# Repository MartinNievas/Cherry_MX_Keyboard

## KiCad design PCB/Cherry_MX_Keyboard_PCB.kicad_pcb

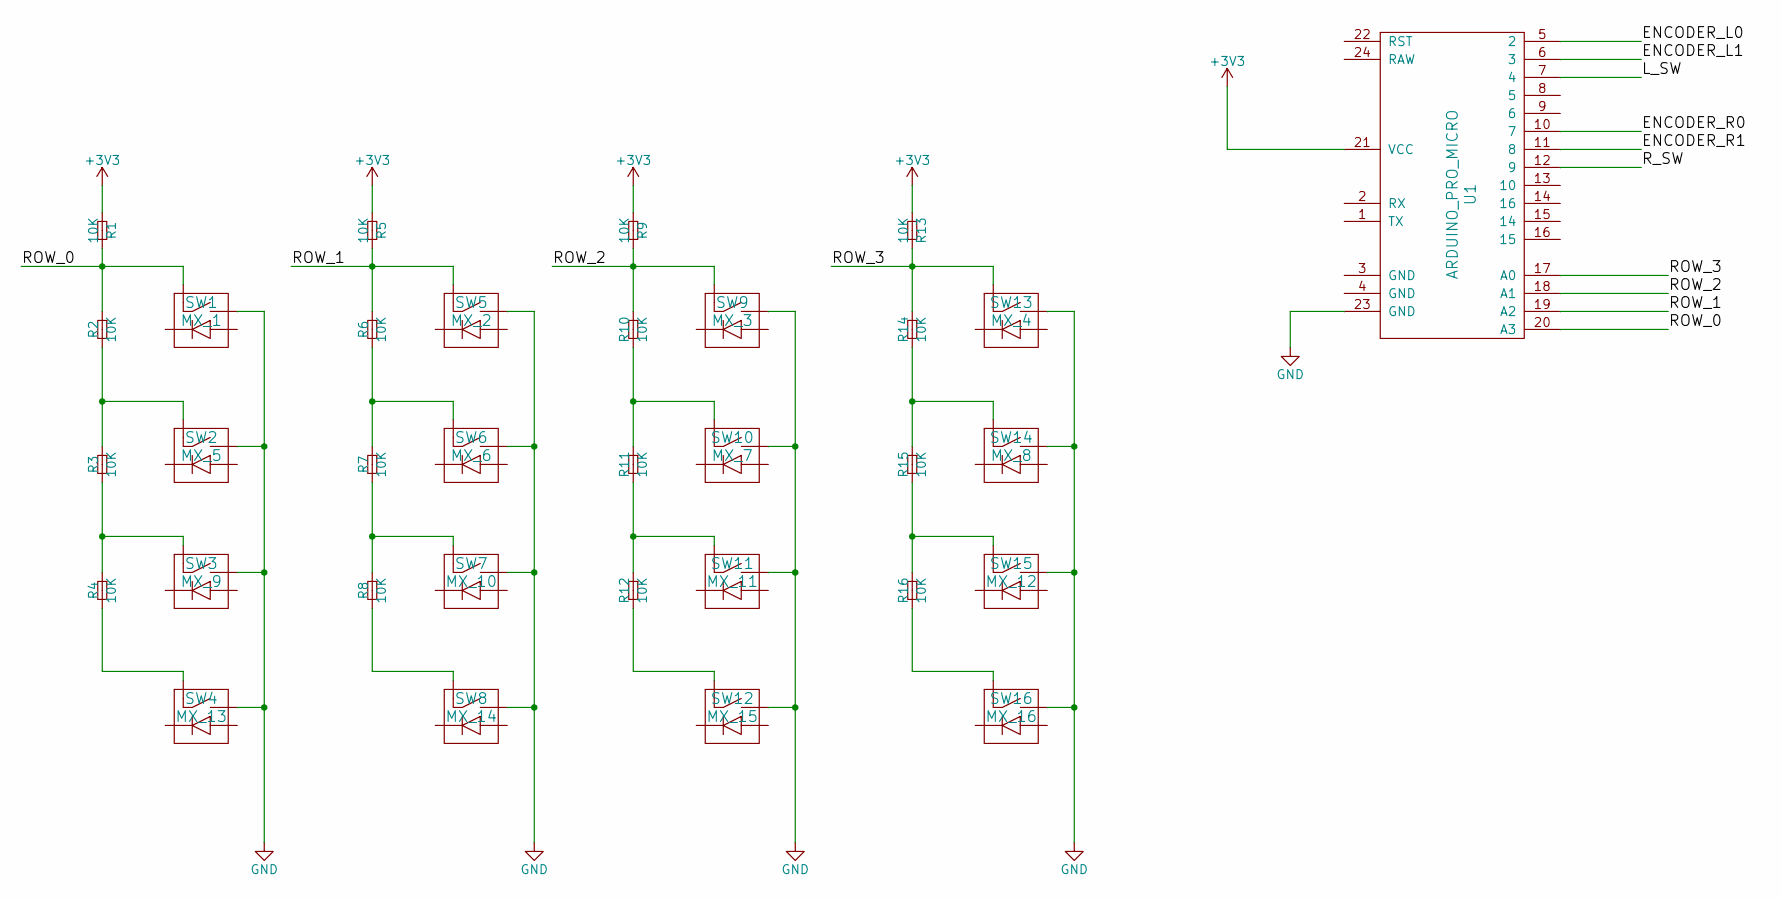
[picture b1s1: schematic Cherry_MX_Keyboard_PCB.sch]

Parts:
R1, R2, R3, R4, R5, R6, R7, R8, R9, R10, R11, R12, R13, R14, R15, R16: 10K; R4
SW1: MX_1; SW_PCB_4PIN
SW2: MX_5; SW_PCB_4PIN
SW3: MX_9; SW_PCB_4PIN
SW4: MX_13; SW_PCB_4PIN
SW5: MX_2; SW_PCB_4PIN
SW6: MX_6; SW_PCB_4PIN
SW7: MX_10; SW_PCB_4PIN
SW8: MX_14; SW_PCB_4PIN
SW9: MX_3; SW_PCB_4PIN
SW10: MX_7; SW_PCB_4PIN
SW11: MX_11; SW_PCB_4PIN
SW12: MX_15; SW_PCB_4PIN
SW13: MX_4; SW_PCB_4PIN
SW14: MX_8; SW_PCB_4PIN
SW15: MX_12; SW_PCB_4PIN
SW16: MX_16; SW_PCB_4PIN
U1: ARDUINO_PRO_MICRO

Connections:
+3V3: R1.2 (B), R5.2 (B), R9.2 (B), R13.2 (B), U1.21 (VCC)
/ENCODER_L0: U1.5 (2)
/ENCODER_L1: U1.6 (3)
/ENCODER_R0: U1.10 (7)
/ENCODER_R1: U1.11 (8)
/L_SW: U1.7 (4)
/ROW_0: R1.1 (A), R2.1 (A), SW1.1 (A), U1.20 (A3)
/ROW_1: R5.1 (A), R6.1 (A), SW5.1 (A), U1.19 (A2)
/ROW_2: R9.1 (A), R10.1 (A), SW9.1 (A), U1.18 (A1)
/ROW_3: R13.1 (A), R14.1 (A), SW13.1 (A), U1.17 (A0)
/R_SW: U1.12 (9)
GND: SW1.2 (B), SW2.2 (B), SW3.2 (B), SW4.2 (B), SW5.2 (B), SW6.2 (B), SW7.2 (B), SW8.2 (B), SW9.2 (B), SW10.2 (B), SW11.2 (B), SW12.2 (B), SW13.2 (B), SW14.2 (B), SW15.2 (B), SW16.2 (B), U1.23 (GND)
unnamed: R2.2 (B), R3.1 (A), SW2.1 (A)
unnamed: R3.2 (B), R4.1 (A), SW3.1 (A)
unnamed: R4.2 (B), SW4.1 (A)
unnamed: R6.2 (B), R7.1 (A), SW6.1 (A)
unnamed: R7.2 (B), R8.1 (A), SW7.1 (A)
unnamed: R8.2 (B), SW8.1 (A)
unnamed: R10.2 (B), R11.1 (A), SW10.1 (A)
unnamed: R11.2 (B), R12.1 (A), SW11.1 (A)
unnamed: R12.2 (B), SW12.1 (A)
unnamed: R14.2 (B), R15.1 (A), SW14.1 (A)
unnamed: R15.2 (B), R16.1 (A), SW15.1 (A)
unnamed: R16.2 (B), SW16.1 (A)

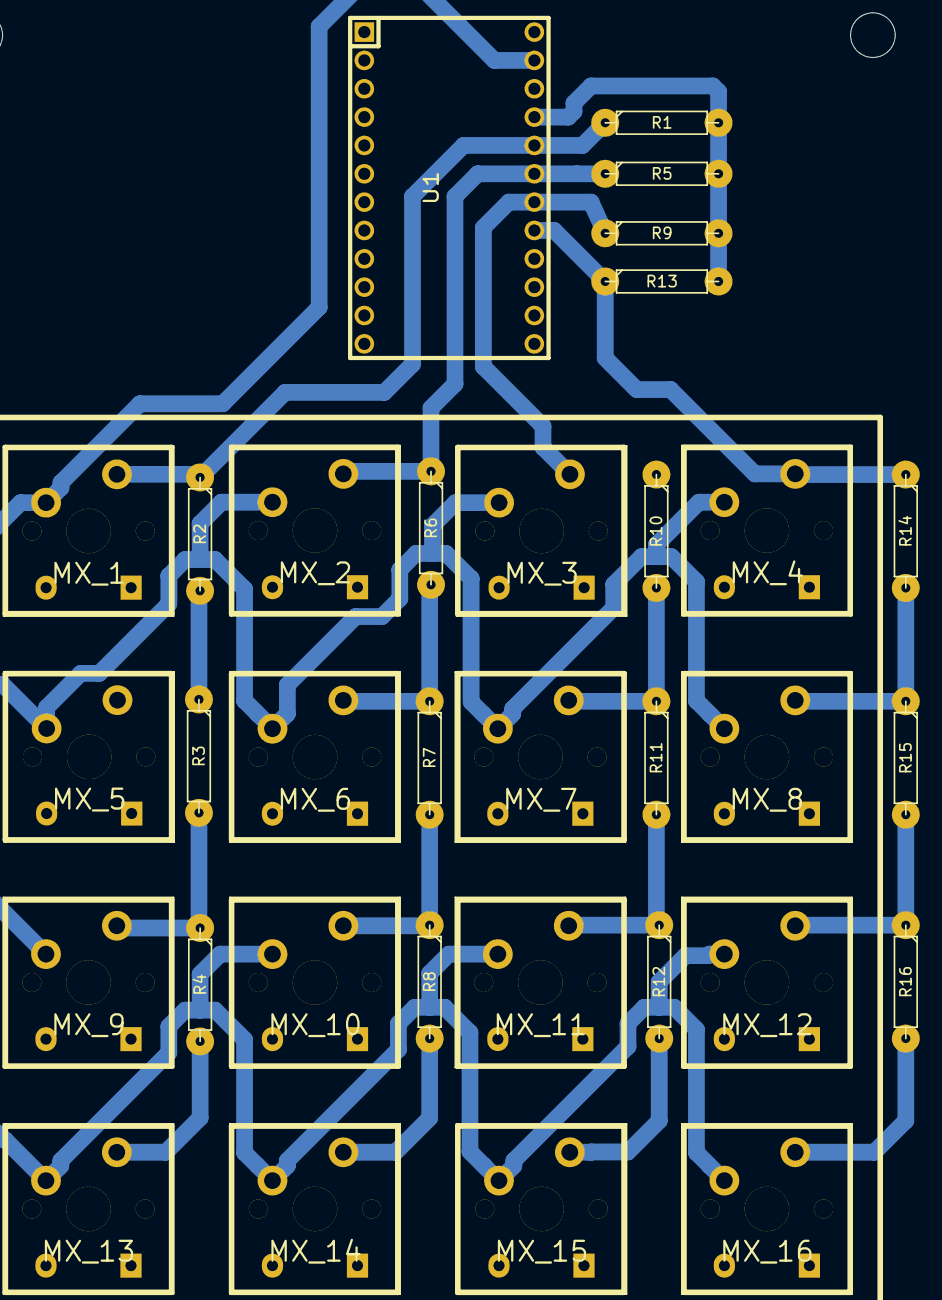
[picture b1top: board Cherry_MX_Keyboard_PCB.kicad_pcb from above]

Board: 2 copper layers, 34 parts (0 on the bottom side), 18 nets.

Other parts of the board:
svg2mod: G***; cherryMX

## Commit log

2017-08-13 keyboard pcb V.0.1
2017-08-20 keyboard PCB V 0.2
2017-08-21 3D model for print
2017-08-21 3D model PCB
